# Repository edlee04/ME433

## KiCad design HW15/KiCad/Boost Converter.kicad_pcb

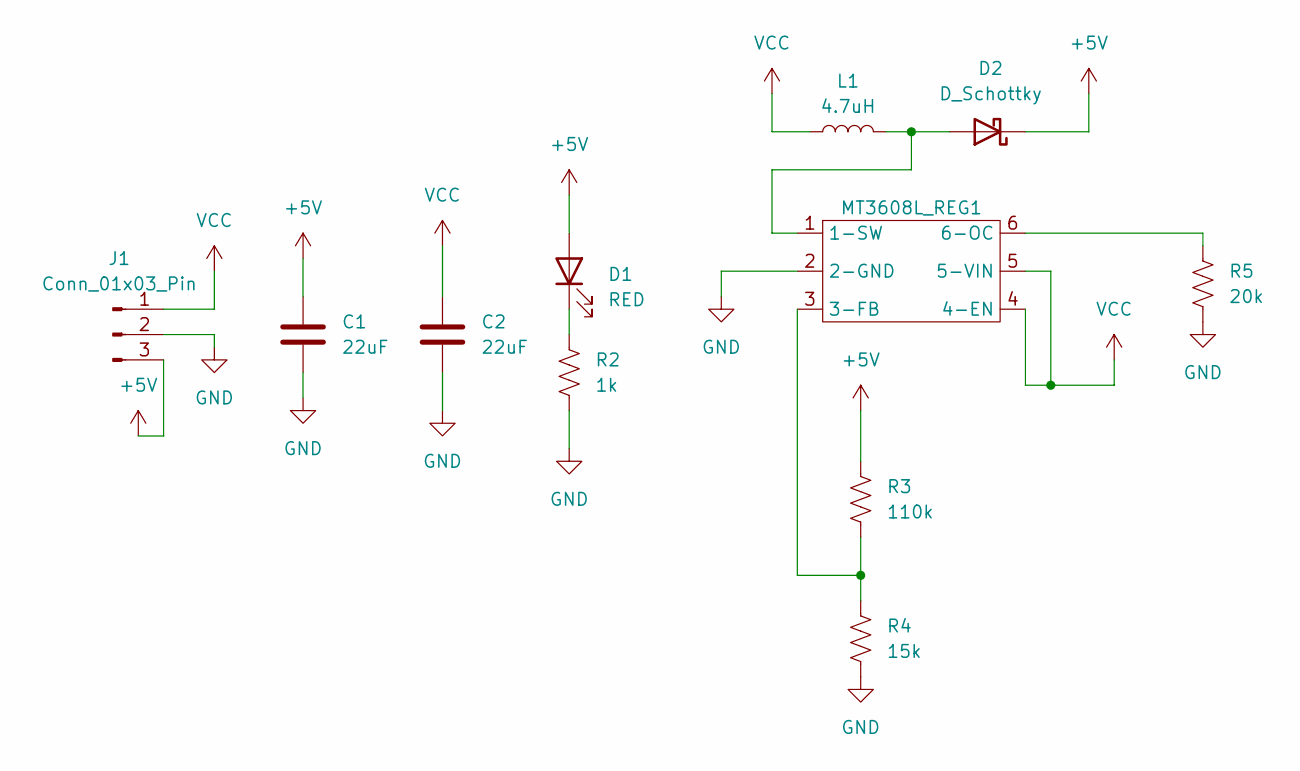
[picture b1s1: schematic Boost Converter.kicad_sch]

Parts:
C1, C2: 22uF; C_0805_2012Metric
D1: RED; LED_D3.0mm
D2: D_Schottky; D_SMA
J1: Conn_01x03_Pin; PinSocket_1x03_P2.54mm_Vertical
L1: 4.7uH; L_0603_1608Metric
MT3608L_REG1: PinSocket_2x03_P2.54mm_Horizontal
R2: 1k; R_0603_1608Metric
R3: 110k; R_0402_1005Metric
R4: 15k; R_0603_1608Metric
R5: 20k; R_0603_1608Metric

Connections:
+5V: C1.1, D1.2 (A), D2.1 (K), J1.3, R3.1
GND: C1.2, C2.2, J1.2, MT3608L_REG1.2 (2-GND), R2.2, R4.2, R5.2
unnamed: D1.1 (K), R2.1
unnamed: D2.2 (A), L1.2, MT3608L_REG1.1 (1-SW)
unnamed: MT3608L_REG1.3 (3-FB), R3.2, R4.1
unnamed: MT3608L_REG1.6 (6-OC), R5.1
VCC: C2.1, J1.1, L1.1, MT3608L_REG1.4 (4-EN), MT3608L_REG1.5 (5-VIN)

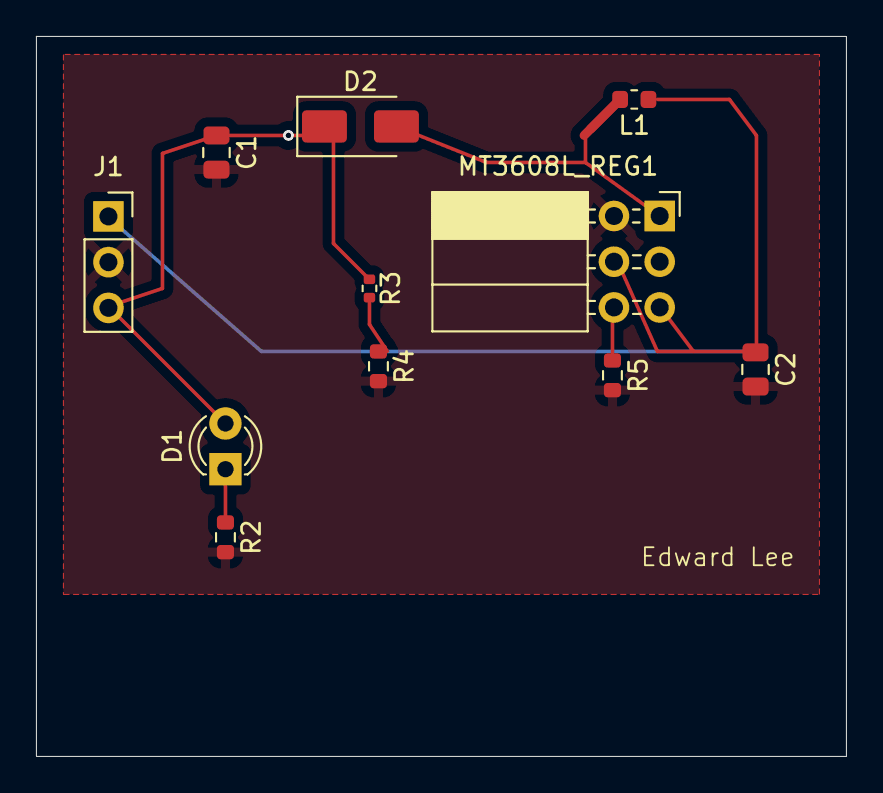
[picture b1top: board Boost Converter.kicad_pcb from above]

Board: 2 copper layers, 45.0 x 40.0 mm, 11 parts (0 on the bottom side), 7 nets.

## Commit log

2025-04-11 Adding HW2
2025-04-11 Revert "Adding HW2"
    This reverts commit f822054cfc27652170e4a570904ef5a39c7bd8f2.
2025-04-11 Adding HW2 (Blink)
2025-04-11 Adding HW3 (ADC Read)
2025-04-16 Adding SPI_DAC
2025-04-20 Adding MathTesting and SPI_RAM
2025-04-21 Adding I2C Blink
2025-04-27 Adding OLED Display
2025-04-28 NeoPixel & Servo Motor
2025-05-05 Adding Multithread CPU
2025-05-13 Adding USB Mouse
2025-05-27 Adding I2C IMU
2025-06-02 Adding Robot CAD
2025-06-03 Adding Reading Camera
2025-06-03 Adding Motor Control
2025-06-03 Adding KiCad
2025-06-05 Adding Robot Assembly
